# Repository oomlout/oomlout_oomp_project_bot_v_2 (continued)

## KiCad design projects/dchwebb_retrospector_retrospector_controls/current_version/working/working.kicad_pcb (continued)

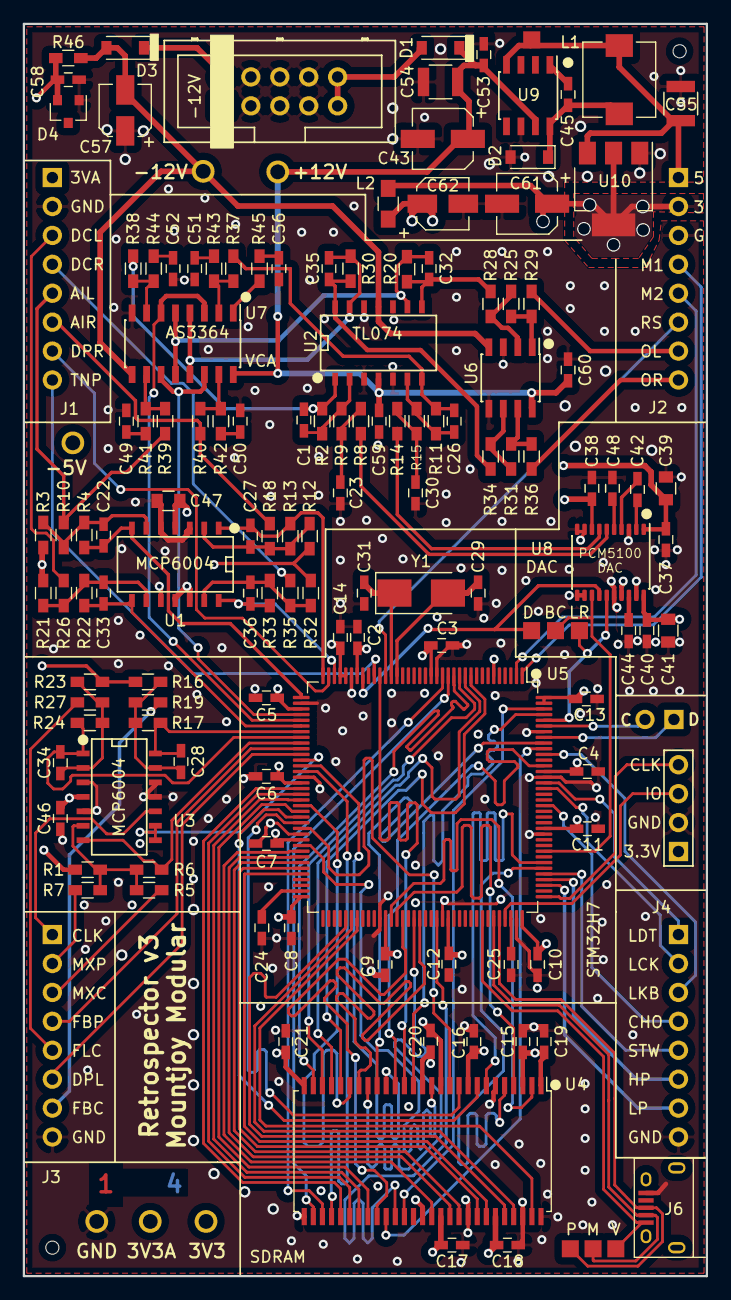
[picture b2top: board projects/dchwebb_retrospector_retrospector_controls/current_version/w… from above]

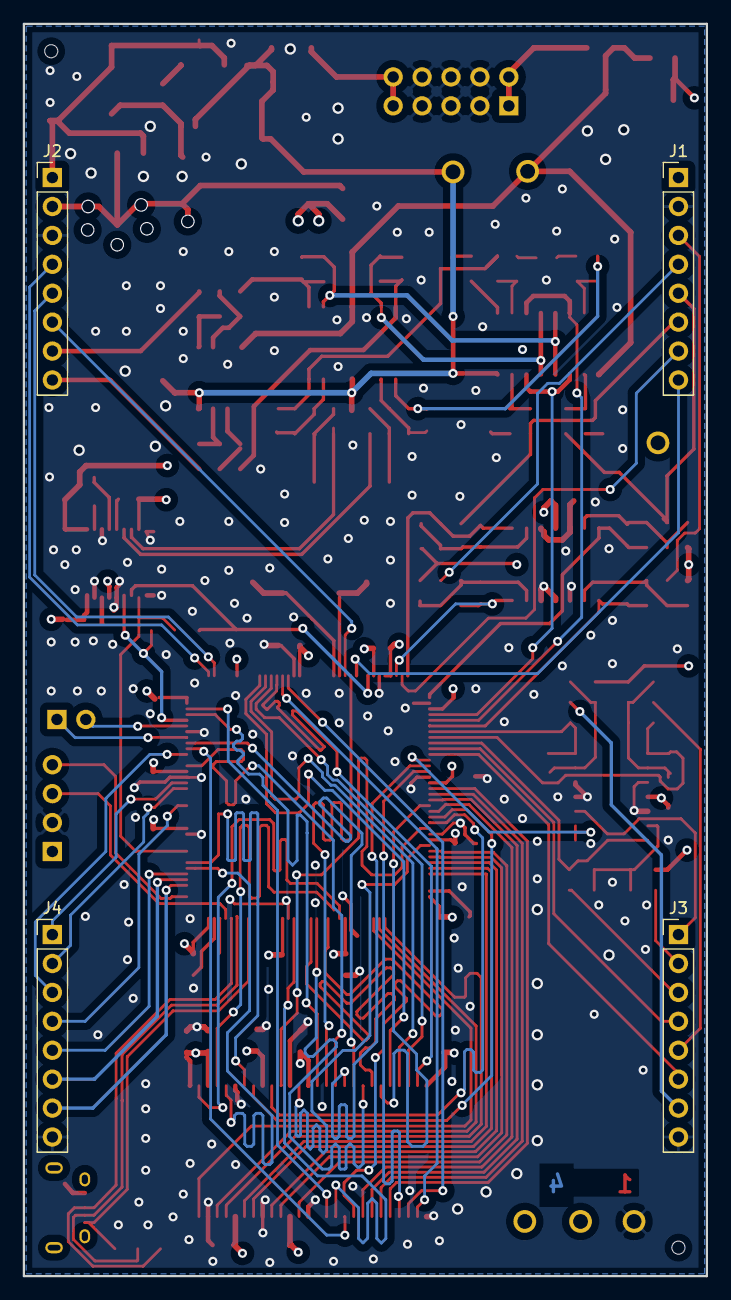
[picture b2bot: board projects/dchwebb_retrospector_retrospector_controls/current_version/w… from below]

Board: 4 copper layers, 60.0 x 110.0 mm, 149 parts (4 on the bottom side), 136 nets.

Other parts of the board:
4_Layer_Marker: 4_Layer_Markers

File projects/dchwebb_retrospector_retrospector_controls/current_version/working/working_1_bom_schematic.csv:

"Source:","C:\gh\oomlout_oomp_project_bot_v_2\projects\dchwebb_retrospector_retrospector_controls\current_version\working\working_1.kicad_sch"
"Date:","01/10/2023 06:39:55"
"Tool:","Eeschema 7.0.6"
"Generator:","C:/Program Files/KiCad/7.0/bin/scripting/plugins/bom_csv_grouped_by_value_with_fp.py"
"Component Count:","149"
"Ref","Qnty","Value","Cmp name","Footprint","Description","Vendor","DNP"
"C1, C26, C32, C35","4","100pF","C_Small","Capacitors_SMD:C_0603_HandSoldering","Unpolarized capacitor, small symbol","",""
"C2, C3, C4, C5, C6, C7, C8, C9, C10, C11, C12, C13, C14, C15, C16, C17, C18, C19, C20, C21, C37, C38, C40, C44, C53, C58","26","100nF","C_Small","Capacitors_SMD:C_0603_HandSoldering","Unpolarized capacitor, small symbol","",""
"C22, C27, C28, C33, C34, C36","6","1.5nF","C_Small","Capacitors_SMD:C_0603_HandSoldering","Unpolarized capacitor, small symbol","",""
"C23, C30","2","1nF","C_Small","Capacitors_SMD:C_0603_HandSoldering","Unpolarized capacitor, small symbol","",""
"C24, C25, C42, C46, C48, C59, C60","7","2.2uF","C_Small","Capacitors_SMD:C_0603_HandSoldering","Unpolarized capacitor, small symbol","",""
"C29, C31","2","30pF","C_Small","Capacitors_SMD:C_0603_HandSoldering","Unpolarized capacitor, small symbol","",""
"C39, C41, C47","3","10uF","C_Small","Capacitors_SMD:C_0805","Unpolarized capacitor, small symbol","",""
"C43, C61","2","47uF","CP_Small","Capacitors_SMD:CP_Elec_5x5.8","","",""
"C45, C56","2","10nF","C_Small","Capacitors_SMD:C_0603_HandSoldering","Unpolarized capacitor, small symbol","",""
"C49, C50, C51, C52","4","560pF","C_Small","Capacitors_SMD:C_0603_HandSoldering","Unpolarized capacitor, small symbol","",""
"C54","1","22uF","C_Small","Capacitors_SMD:C_1210","Unpolarized capacitor, small symbol","",""
"C55","1","47uF","C_Small","Capacitors_SMD:C_1210","Unpolarized capacitor, small symbol","",""
"C57, C62","2","22uF","CP_Small","Capacitors_SMD:CP_Elec_4x5.8","","",""
"D1, D2, D3","3","1N5819","1N5819","Diodes_SMD:D_SOD-123","40V 1A Schottky Barrier Rectifier Diode, DO-41","",""
"D4","1","LM4040DBZ-5","LM4040DBZ-10","TO_SOT_Packages_SMD:SOT-23","10.00V Precision Micropower Shunt Voltage Reference, SOT-23","",""
"H1, H2","2","JLC_Tooling_Hole","MountingHole","Custom_Footprints:JLC_SMT_Tooling_Hole","Mounting Hole without connection","",""
"J1, J2, J3, J4","4","Conn_01x08_Male","Conn_01x08_Male","Pin_Headers:Pin_Header_Straight_1x08_Pitch2.54mm","Generic connector, single row, 01x08, script generated (kicad-library-utils/schlib/autogen/connector/)","",""
"J5","1","SWD_Header","Conn_01x04_Male","Custom_Footprints:SWD_header","Generic connector, single row, 01x04, script generated (kicad-library-utils/schlib/autogen/connector/)","",""
"J6","1","USB_B_Micro","USB_B_Micro","Custom_Footprints:USB_Micro-B_Amphenol","USB Micro Type B connector","",""
"J7","1","Eurorack_10_pin_power","Eurorack_10_pin_power","Custom_Footprints:Eurorack_10_pin_header","","",""
"J8","1","I2C_TestPoint","Conn_01x02_Female","Pin_Headers:Pin_Header_Straight_1x02_Pitch2.54mm","Generic connector, single row, 01x02, script generated (kicad-library-utils/schlib/autogen/connector/)","",""
"L1","1","68uH","L_Small","Custom_Footprints:TDK_Inductor_6.9x7.2","Inductor, small symbol","",""
"L2","1","L","L","Inductors_SMD:L_0805_HandSoldering","Inductor","",""
"R1","1","75k","R","Resistors_SMD:R_0603_HandSoldering","Resistor","",""
"R2, R6, R7, R10, R11, R18, R22, R24, R33","9","47k","R","Resistors_SMD:R_0603_HandSoldering","Resistor","",""
"R3, R12","2","20k","R","Resistors_SMD:R_0603_HandSoldering","Resistor","",""
"R4, R13","2","6k8","R","Resistors_SMD:R_0603_HandSoldering","Resistor","",""
"R5, R16","2","91k","R","Resistors_SMD:R_0603_HandSoldering","Resistor","",""
"R8, R14, R46","3","2k2","R_Small","Resistors_SMD:R_0603_HandSoldering","Resistor, small symbol","",""
"R9, R15, R25, R28, R31, R34","6","10k","R","Resistors_SMD:R_0603_HandSoldering","Resistor","",""
"R17","1","56k","R","Resistors_SMD:R_0603_HandSoldering","Resistor","",""
"R19, R26, R27, R35","4","100k","R","Resistors_SMD:R_0603_HandSoldering","Resistor","",""
"R20, R30, R37, R38, R39, R40","6","30k","R_Small","Resistors_SMD:R_0603_HandSoldering","Resistor, small symbol","",""
"R21, R23, R32","3","68k","R","Resistors_SMD:R_0603_HandSoldering","Resistor","",""
"R29, R36","2","1k","R","Resistors_SMD:R_0603_HandSoldering","Resistor","",""
"R41, R42, R43, R44","4","510R","R_Small","Resistors_SMD:R_0603_HandSoldering","Resistor, small symbol","",""
"R45","1","100R","R_Small","Resistors_SMD:R_0603_HandSoldering","Resistor, small symbol","",""
"TP1, TP2, TP3, TP4, TP5, TP6","6","TestPoint","TestPoint","Custom_Footprints:1.3mm_Test_Point","test point","",""
"TP7, TP8, TP9, TP10, TP11, TP12, TP13","7","TestPoint","TestPoint","Measurement_Points:Measurement_Point_Square-SMD-Pad_Small","test point","",""
"U1, U3","2","MCP6004","MCP6004","SMD_Packages:SOIC-14_N","1MHz, Low-Power Op Amp, DIP-14/SOIC-14/TSSOP-14","",""
"U2","1","TL074","TL074","SMD_Packages:SOIC-14_N","Quad Low-Noise JFET-Input Operational Amplifiers, DIP-14/SOIC-14","",""
"U4","1","IS42S16800F-7TLI","IS42S16160","Custom_Footprints:TSOP-II-54_22.2x10.16mm_P0.8mm","","",""
"U5","1","STM32H743ZITx","STM32H743ZITx","Package_QFP:LQFP-144_20x20mm_P0.5mm","ARM Cortex-M7 MCU, 2048KB flash, 864KB RAM, 400MHz, 1.7-3.6V, 114 GPIO, LQFP-144","",""
"U6","1","TL072","TL072","Housings_SOIC:SOIC-8_3.9x4.9mm_Pitch1.27mm","Dual Low-Noise JFET-Input Operational Amplifiers, DIP-8/SOIC-8","",""
"U7","1","AS3364","SSI2164","Housings_SOIC:SOIC-16_3.9x9.9mm_Pitch1.27mm","Quad VCA, SOIC-16","",""
"U8","1","PCM5100APW","PCM5100APW","Custom_Footprints:SSOP-20_4.4x6.5mm_Pitch0.65mm_Round_Pads","2VRMS DirectPath, 100dB Audio Stereo DAC with 32-bit, 384kHz PCM Interface, TSSOP-20","",""
"U9","1","LM2675M-5","LM2675M-5","Housings_SOIC:SOIC-8_3.9x4.9mm_Pitch1.27mm","5V, 1A Step-Down Voltage Regulator, SO-8","",""
"U10","1","LD1117-3.3-4Tab","LD1117-3.3-4Tab","TO_SOT_Packages_SMD:SOT-223-3_TabPin2","1A Low Dropout regulator, positive, 3.3V fixed output, SOT-223","",""
"U11","1","Hyperram_BGA","Hyperram_BGA","","","",""
"Y1","1","8MHz 20pF","Crystal","Crystals:Crystal_SMD_5032-2pin_5.0x3.2mm_HandSoldering","Two pin crystal","",""

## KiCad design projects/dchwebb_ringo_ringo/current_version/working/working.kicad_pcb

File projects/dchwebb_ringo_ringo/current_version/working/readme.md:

# ringo
 
## summary 
* id: dchwebb_ringo_ringo
* user: dchwebb
* name: ringo
* board: ringo
* repo: https://github.com/dchwebb/Ringo
* src_file_repo_kicad_pcb: Ringo.kicad_pcb
* src_file_repo_kicad_pcb_link: https://github.com/dchwebb/Ringo/tree/master/Ringo.kicad_pcb
* src_file_repo_kicad_sch: Ringo.kicad_sch
* src_file_repo_kicad_sch_link: https://github.com/dchwebb/Ringo/tree/master/Ringo.kicad_sch

* src_file_repo_sch: 
* src_file_repo_sch_link: https://github.com/dchwebb/Ringo/tree/master/
* full details link: https://github.com/oomlout/oomlout_oomp_project_bot_v_2/tree/main/projects/dchwebb_ringo_ringo/current_version/working

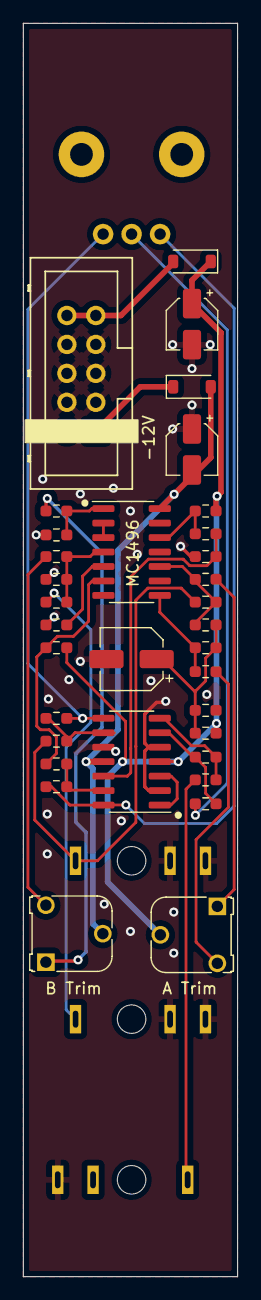
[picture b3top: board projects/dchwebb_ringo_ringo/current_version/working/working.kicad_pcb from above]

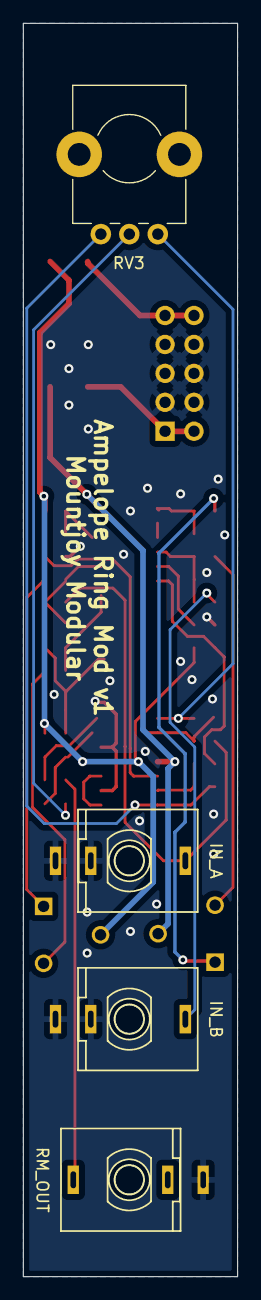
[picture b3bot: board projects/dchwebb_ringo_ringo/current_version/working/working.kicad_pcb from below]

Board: 2 copper layers, 18.8 x 110.0 mm, 38 parts (4 on the bottom side), 30 nets.

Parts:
C1: 100uF 16V; CP_Elec_5x5.7
C2, C3: 22uF; CP_Elec_4x5.8
D1, D2: 1N5819; D_SOD-123
J1: IN_A; THONKICONN_hole
J2: IN_B; THONKICONN_hole
J3: RM_OUT; THONKICONN_hole
J4: Eurorack_10_pin_power; Eurorack_10_pin_header
R1, R2: 1K5; R_0603_1608Metric_Pad0.98x0.95mm_HandSolder
R3, R4: 12K; R_0603_1608Metric_Pad0.98x0.95mm_HandSolder
R5, R7, R19, R22: 2K7; R_0603_1608Metric_Pad0.98x0.95mm_HandSolder
R6, R12, R15, R18, R23, R24: 15K; R_0603_1608Metric_Pad0.98x0.95mm_HandSolder
R8, R9: 1K2; R_0603_1608Metric_Pad0.98x0.95mm_HandSolder
R10: 68K; R_0603_1608Metric_Pad0.98x0.95mm_HandSolder
R11, R16: 180K; R_0603_1608Metric_Pad0.98x0.95mm_HandSolder
R13: 10K; R_0603_1608Metric_Pad0.98x0.95mm_HandSolder
R14: 470; R_0603_1608Metric_Pad0.98x0.95mm_HandSolder
R17, R20, R21: 6K8; R_0603_1608Metric_Pad0.98x0.95mm_HandSolder
RV1: 500; Potentiometer_Runtron_RM-065_Vertical
RV2: 220; Potentiometer_Runtron_RM-065_Vertical
RV3: R_Potentiometer; Alpha_9mm_Potentiometer_Aligned
U1: MC1496; SOIC-14_3.9x8.7mm_P1.27mm
U2: TL074; SOIC-14_3.9x8.7mm_P1.27mm

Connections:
+12V: D1.2 (A), J4.9, J4.10
-12V: D2.1 (K), J4.1, J4.2
/A_IN: J1.3, R11.2, R23.2
/MIX_OUT: R13.2, RV3.2
/MIX_RM: R6.1, RV3.3, U2.14
GND: C1.2, C2.2, C3.1, J1.1, J1.2, J2.1, J2.2, J3.1, J4.3, J4.4, J4.5, J4.6, J4.7, J4.8, R1.2, R17.1, R18.1, R19.1, R22.1, U2.2 (-), U2.5 (+), U2.10 (+)
unnamed: C1.1, R1.1, R2.2, R5.2, R7.2
unnamed: J2.3, R16.2
unnamed: J3.3, R14.1
unnamed: R3.1, RV1.1
unnamed: R4.1, RV1.3
unnamed: R4.2, R5.1, U1.8 (C_IN)
unnamed: R10.1, R14.2, U2.7
unnamed: R10.2, R13.1, U2.6 (-)
unnamed: R3.2, R7.1, R11.1, U1.10 (C_IN)
unnamed: R6.2, R12.1, U2.13 (-)
unnamed: R8.2, R12.2, U1.6 (OUT)
unnamed: R15.1, R18.2, U2.12 (+)
unnamed: R9.2, R15.2, U1.12 (OUT)
unnamed: R16.1, R19.2, R20.2, U1.4 (S_IN)
unnamed: R17.2, U1.5 (BIAS)
unnamed: R20.1, RV2.3
unnamed: R21.1, RV2.1
unnamed: R21.2, R22.2, U1.1 (S_IN)
unnamed: R23.1, R24.2, U2.9 (-)
unnamed: R24.1, RV3.1, U2.8
unnamed: U1.2 (GAIN), U1.3 (GAIN)
unnamed: U2.1, U2.3 (+)
VCC: C2.1, D1.1 (K), R2.1, R8.1, R9.1, RV1.2, U2.4 (V+)
VEE: C3.2, D2.2 (A), RV2.2, U1.14 (VEE), U2.11 (V-)

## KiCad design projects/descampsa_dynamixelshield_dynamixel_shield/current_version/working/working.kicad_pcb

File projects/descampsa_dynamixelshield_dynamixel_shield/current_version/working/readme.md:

# dynamixelshield
 
## summary 
* id: descampsa_dynamixelshield_dynamixel_shield
* user: descampsa
* name: dynamixelshield
* board: dynamixel_shield
* repo: https://github.com/descampsa/DynamixelShield
* src_file_repo_kicad_pcb: dynamixel_shield.kicad_pcb
* src_file_repo_kicad_pcb_link: https://github.com/descampsa/DynamixelShield/tree/master/dynamixel_shield.kicad_pcb

* src_file_repo_sch: dynamixel_shield.sch
* src_file_repo_sch_link: https://github.com/descampsa/DynamixelShield/tree/master/dynamixel_shield.sch
* full details link: https://github.com/oomlout/oomlout_oomp_project_bot_v_2/tree/main/projects/descampsa_dynamixelshield_dynamixel_shield/current_version/working

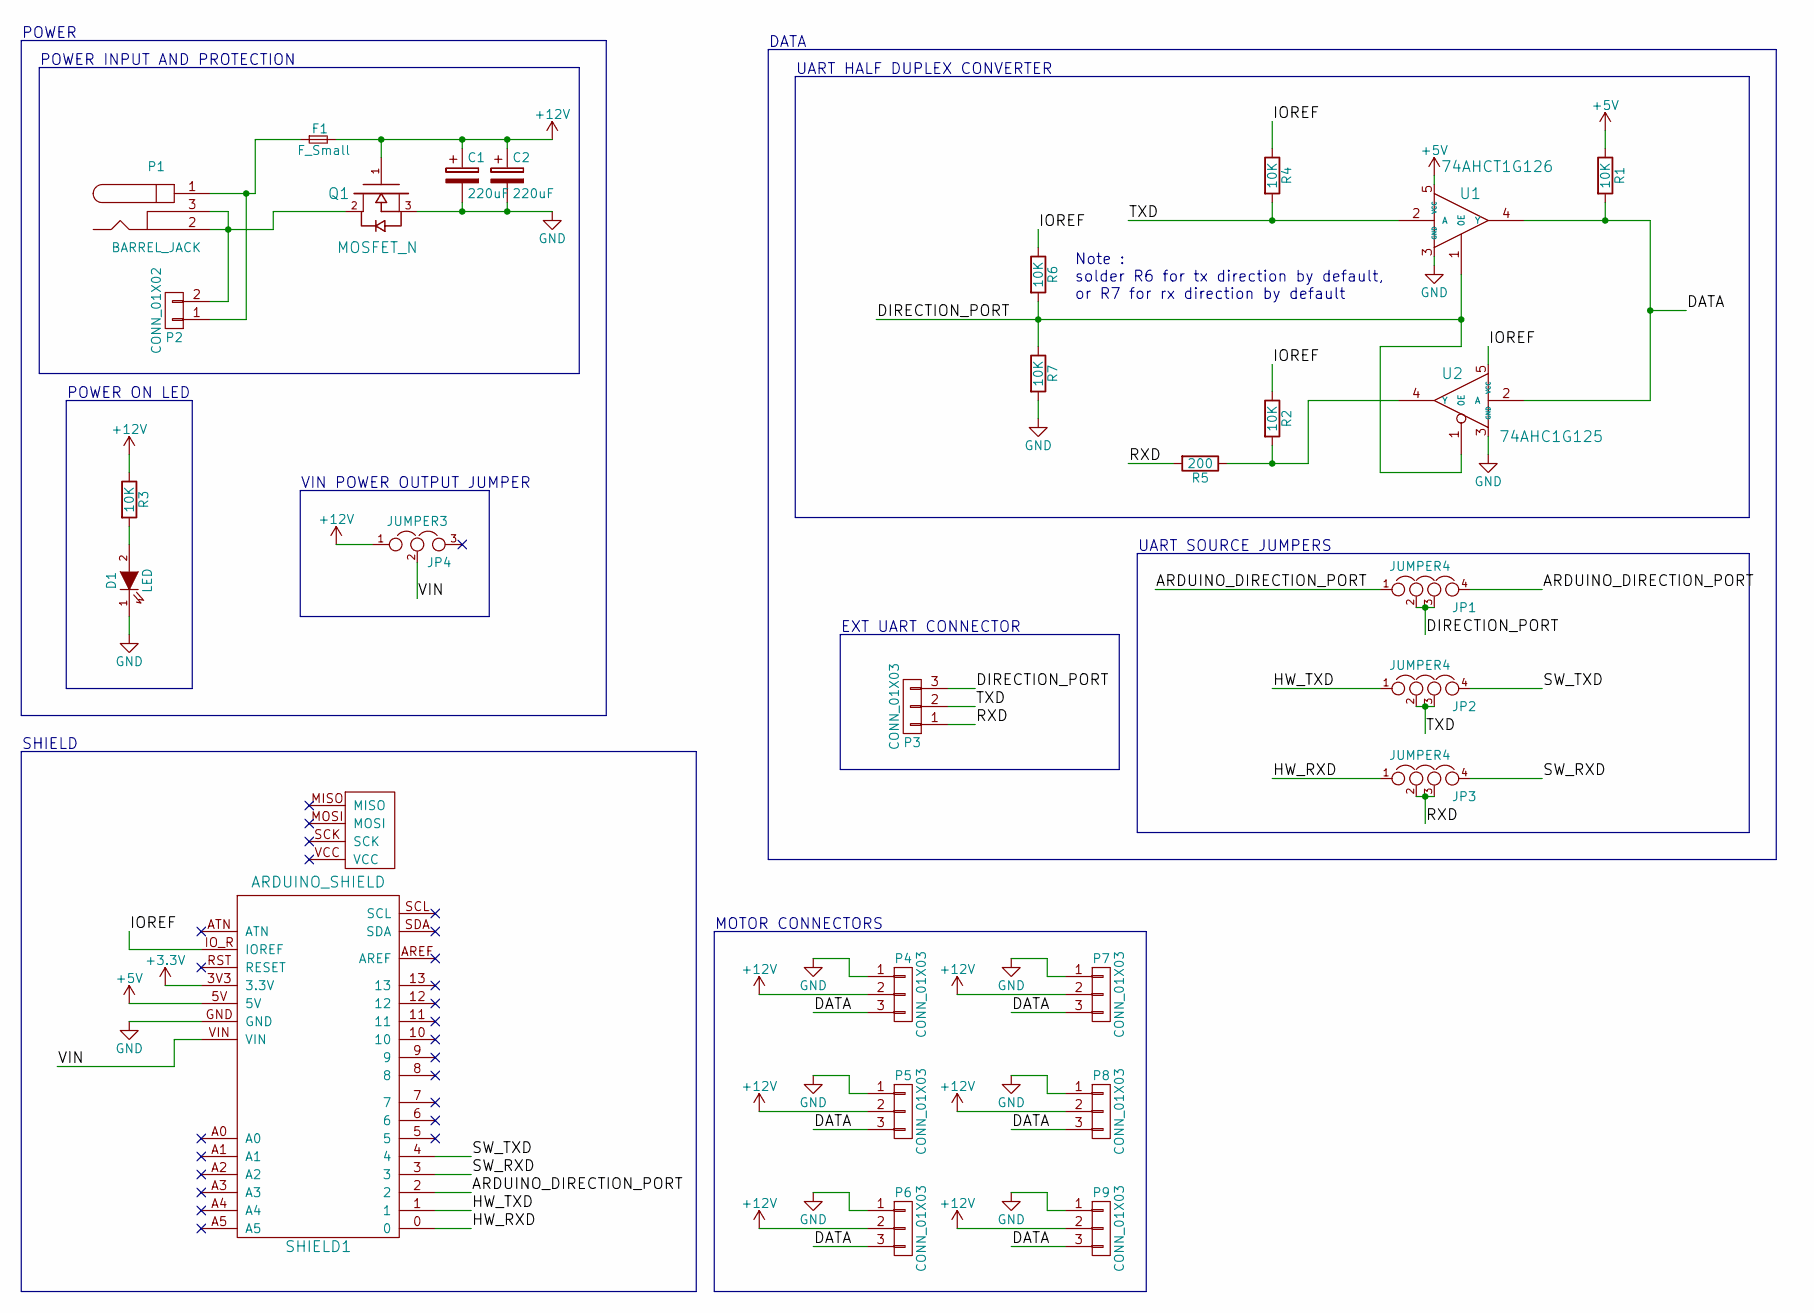
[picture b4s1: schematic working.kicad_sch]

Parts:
C1, C2: 220uF; CP_Elec_6.3x7.7
D1: LED; LED_0603
F1: F_Small; Fuseholder5x20_horiz_lateral
JP1, JP2, JP3: JUMPER4; Pin_Header_Straight_1x04
JP4: JUMPER3; Pin_Header_Straight_1x03
P1: BARREL_JACK
P2: CONN_01X02; bornier2
P3: CONN_01X03; Pin_Header_Angled_1x03
P4, P5, P6, P7: CONN_01X03; Molex_spox_1x3_right
P8, P9: CONN_01X03; Molex_spox_1x3_straight
Q1: MOSFET_N; TO-252-2Lead
R1, R2, R3, R4, R6, R7: 10K; R_0603_HandSoldering
R5: 200; R_0603_HandSoldering
SHIELD1: ARDUINO_SHIELD; Arduino_shield_dynamixel
U1: 74AHCT1G126; SOT-353
U2: 74AHC1G125; SOT-353

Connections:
+3V3: SHIELD1.3V3 (3.3V)
+5V: R1.1, SHIELD1.5V, U1.5 (VCC)
+12V: C1.1, C2.1, F1.2, JP4.1, P4.2, P5.2, P6.2, P7.2, P8.2, P9.2, Q1.1 (G), R3.1
/ARDUINO_DIRECTION_PORT: JP1.1, JP1.4, SHIELD1.2
/DATA: P4.3, P5.3, P6.3, P7.3, P8.3, P9.3, R1.2, U1.4 (Y), U2.2 (A)
/DIRECTION_PORT: JP1.2, JP1.3, P3.3, R6.2, R7.1, U1.1 (0E), U2.1 (0E)
/HW_RXD: JP3.1, SHIELD1.0
/HW_TXD: JP2.1, SHIELD1.1
/IOREF: R2.1, R4.1, R6.1, SHIELD1.IO_R (IOREF), U2.5 (VCC)
/RXD: JP3.2, JP3.3, P3.1, R5.2
/SW_RXD: JP3.4, SHIELD1.3
/SW_TXD: JP2.4, SHIELD1.4
/TXD: JP2.2, JP2.3, P3.2, R4.2, U1.2 (A)
/VIN: JP4.2, SHIELD1.VIN
GND: C1.2, C2.2, D1.1 (K), P4.1, P5.1, P6.1, P7.1, P8.1, P9.1, Q1.3 (S), R7.2, SHIELD1.GND, U1.3 (GND), U2.3 (GND)
unnamed: D1.2 (A), R3.2
unnamed: F1.1, P1.1, P2.1
unnamed: P1.2, P1.3, P2.2, Q1.2 (D)
unnamed: R2.2, R5.1, U2.4 (Y)

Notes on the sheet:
EXT UART CONNECTOR
SHIELD
POWER
DATA
VIN POWER OUTPUT JUMPER
Note : solder R6 for tx direction by default, or R7 for rx direction by default
UART HALF DUPLEX CONVERTER
POWER INPUT AND PROTECTION
MOTOR CONNECTORS
POWER ON LED
UART SOURCE JUMPERS

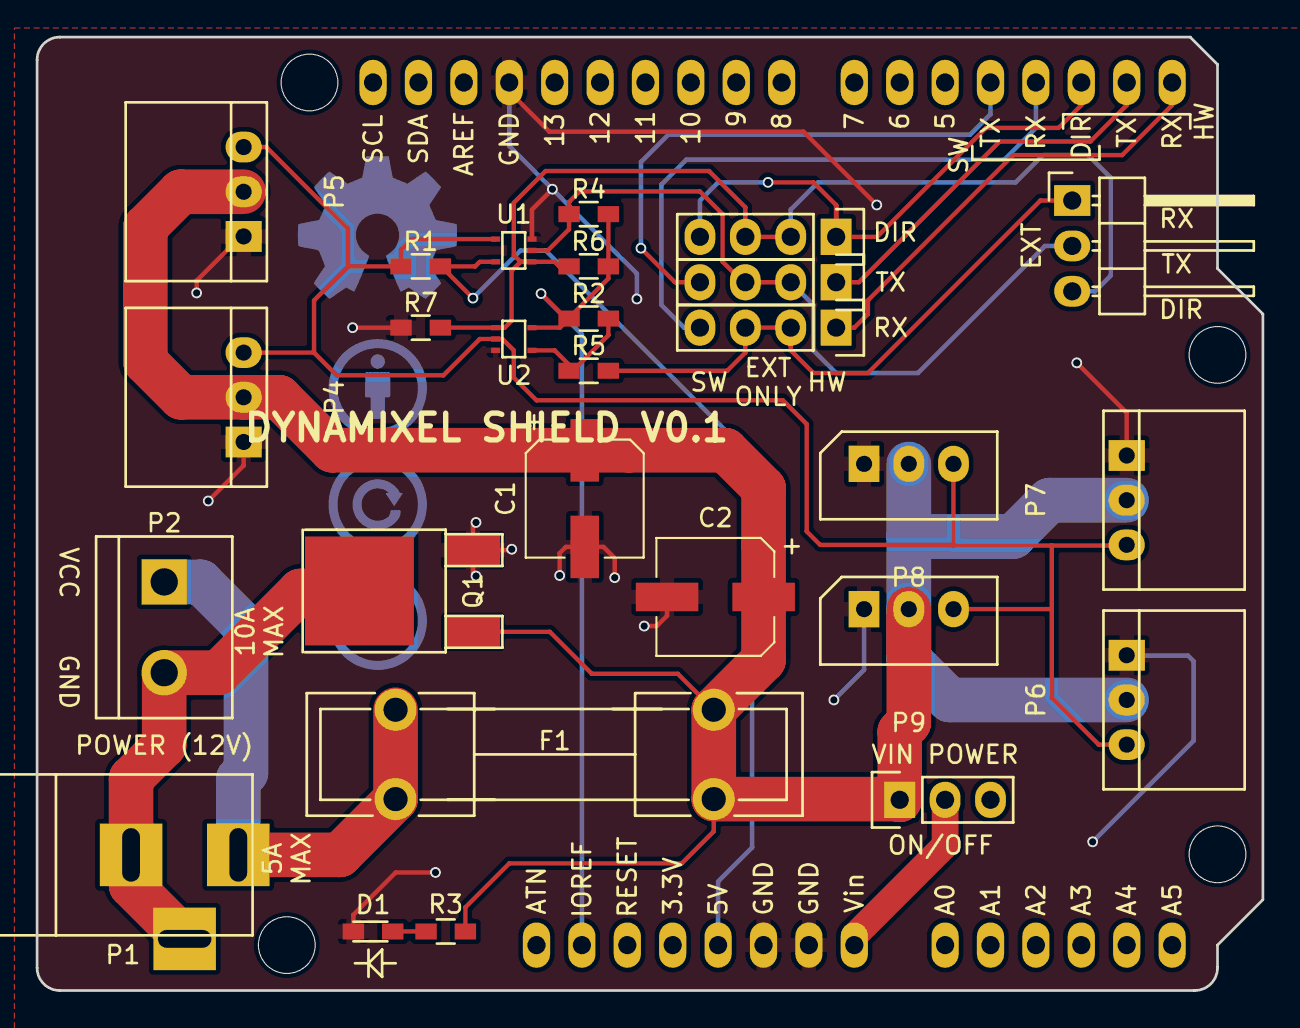
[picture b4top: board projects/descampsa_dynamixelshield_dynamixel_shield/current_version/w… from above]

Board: 2 copper layers, 68.6 x 53.3 mm, 28 parts (0 on the bottom side), 18 nets.

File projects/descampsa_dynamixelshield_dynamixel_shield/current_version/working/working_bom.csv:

"Id";"Designator";"Footprint";"Quantity";"Designation";"Supplier and ref";
1;"JP1,JP2,JP3";"Pin_Header_Straight_1x04";3;"JUMPER4";;;
2;"JP4";"Pin_Header_Straight_1x03";1;"JUMPER3";;;
3;"P2";"bornier2";1;"CONN_01X02";;;
4;"P3";"Pin_Header_Angled_1x03";1;"CONN_01X03";;;
5;"P4,P5,P6,P7";"Molex_spox_1x3_right";4;"CONN_01X03";;;
6;"P8,P9";"Molex_spox_1x3_straight";2;"CONN_01X03";;;
7;"Q1";"TO-252-2Lead";1;"MOSFET_N";;;
8;"R1,R2,R3,R4,R6,R7";"R_0603_HandSoldering";6;"10K";;;
9;"U1";"SOT-353";1;"74AHCT1G126";;;
10;"U2";"SOT-353";1;"74AHC1G125";;;
11;"P1";"BARREL_JACK";1;"BARREL_JACK";;;
12;"F1";"Fuseholder5x20_horiz_lateral";1;"F_Small";;;
13;"D1";"LED_0603";1;"LED";;;
14;"SHIELD1";"Arduino_shield_dynamixel";1;"ARDUINO_SHIELD";;;
15;"R5";"R_0603_HandSoldering";1;"200";;;
16;"C1,C2";"CP_Elec_6.3x7.7";2;"220uF";;;
17;"REF**";"CreativeCommonCopperSmall";1;"CreativeCommonCopper";;;
18;"REF**";"CreativeCommonAttributionCopperSmall";1;"CreativeCommonAttributionCopperSmall";;;
19;"REF**";"CreativeCommonShareAlikeCopperSmall";1;"CreativeCommonShareAlikeCopperSmall";;;

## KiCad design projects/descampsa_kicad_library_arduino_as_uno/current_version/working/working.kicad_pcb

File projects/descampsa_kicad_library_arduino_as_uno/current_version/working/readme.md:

# kicad_library
 
## summary 
* id: descampsa_kicad_library_arduino_as_uno
* user: descampsa
* name: kicad_library
* board: arduino_as_uno
* repo: https://github.com/descampsa/kicad-library
* src_file_repo_kicad_pcb: template/Arduino_As_Uno_R3/Arduino_As_Uno.kicad_pcb
* src_file_repo_kicad_pcb_link: https://github.com/descampsa/kicad-library/tree/master/template/Arduino_As_Uno_R3/Arduino_As_Uno.kicad_pcb

* src_file_repo_sch: template/Arduino_As_Uno_R3/Arduino_As_Uno.sch
* src_file_repo_sch_link: https://github.com/descampsa/kicad-library/tree/master/template/Arduino_As_Uno_R3/Arduino_As_Uno.sch
* full details link: https://github.com/oomlout/oomlout_oomp_project_bot_v_2/tree/main/projects/descampsa_kicad_library_arduino_as_uno/current_version/working

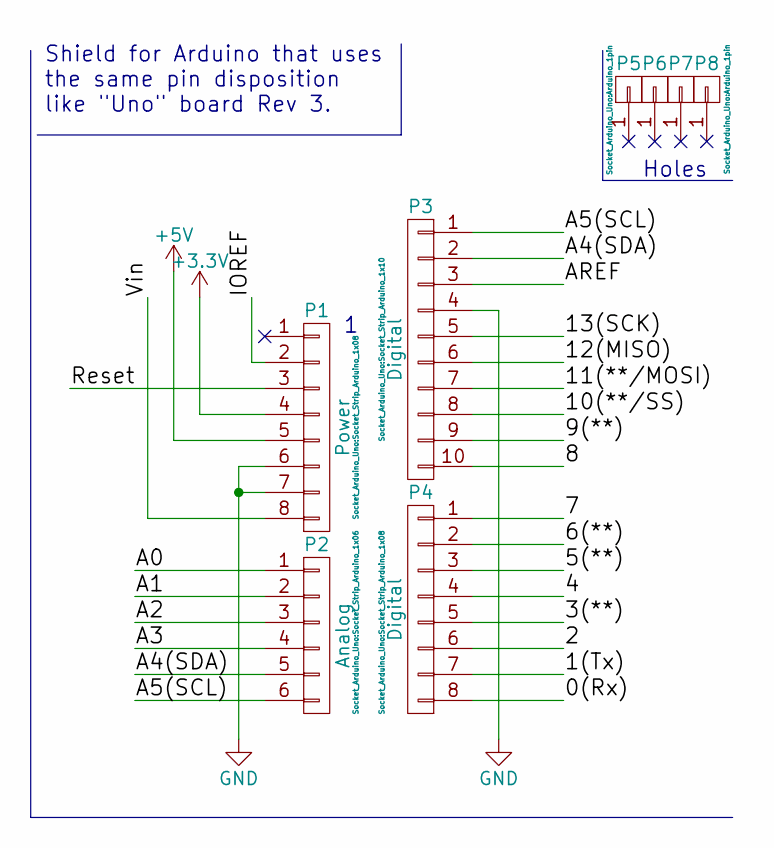
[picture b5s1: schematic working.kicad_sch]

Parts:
P1: Power; Socket_Strip_Arduino_1x08
P2: Analog; Socket_Strip_Arduino_1x06
P3: Digital; Socket_Strip_Arduino_1x10
P4: Digital; Socket_Strip_Arduino_1x08
P5, P6, P7, P8: CONN_01X01; Arduino_1pin

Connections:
+3V3: P1.4
+5V: P1.5
/0(Rx): P4.8
/1(Tx): P4.7
/2: P4.6
/3(**): P4.5
/4: P4.4
/5(**): P4.3
/6(**): P4.2
/7: P4.1
/8: P3.10
/9(**): P3.9
/10(**/SS): P3.8
/11(**/MOSI): P3.7
/12(MISO): P3.6
/13(SCK): P3.5
/A0: P2.1
/A1: P2.2
/A2: P2.3
/A3: P2.4
/A4(SDA): P2.5, P3.2
/A5(SCL): P2.6, P3.1
/AREF: P3.3
/IOREF: P1.2
/Reset: P1.3
/Vin: P1.8
GND: P1.6, P1.7, P3.4

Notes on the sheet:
Holes
Shield for Arduino that uses the same pin disposition like "Uno" board Rev 3.

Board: 2 copper layers, 8 parts (0 on the bottom side), 3 nets, no tracks yet.

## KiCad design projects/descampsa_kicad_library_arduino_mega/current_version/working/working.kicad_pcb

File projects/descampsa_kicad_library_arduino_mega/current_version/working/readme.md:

# kicad_library
 
## summary 
* id: descampsa_kicad_library_arduino_mega
* user: descampsa
* name: kicad_library
* board: arduino_mega
* repo: https://github.com/descampsa/kicad-library
* src_file_repo_kicad_pcb: template/Arduino_Mega_R3/Arduino_Mega.kicad_pcb
* src_file_repo_kicad_pcb_link: https://github.com/descampsa/kicad-library/tree/master/template/Arduino_Mega_R3/Arduino_Mega.kicad_pcb

* src_file_repo_sch: template/Arduino_Mega_R3/Arduino_Mega.sch
* src_file_repo_sch_link: https://github.com/descampsa/kicad-library/tree/master/template/Arduino_Mega_R3/Arduino_Mega.sch
* full details link: https://github.com/oomlout/oomlout_oomp_project_bot_v_2/tree/main/projects/descampsa_kicad_library_arduino_mega/current_version/working

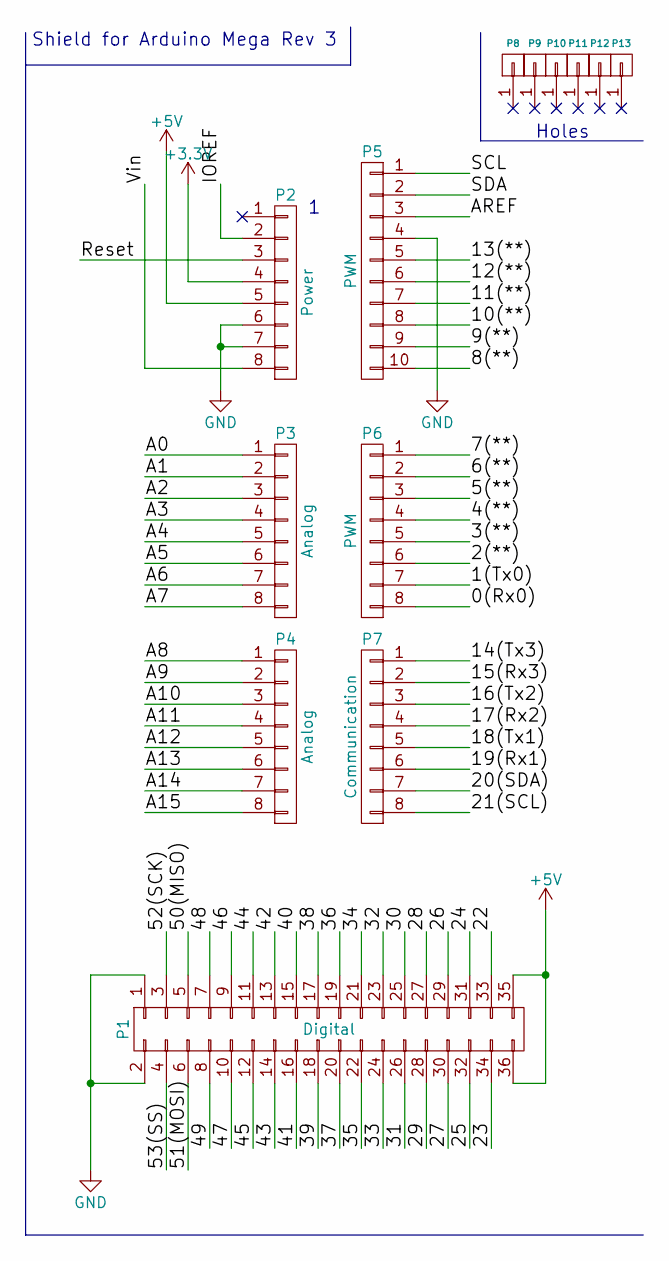
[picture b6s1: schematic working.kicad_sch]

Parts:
P1: Digital; Socket_Strip_Arduino_2x18
P2: Power; Socket_Strip_Arduino_1x08
P3, P4: Analog; Socket_Strip_Arduino_1x08
P5: PWM; Socket_Strip_Arduino_1x10
P6: PWM; Socket_Strip_Arduino_1x08
P7: Communication; Socket_Strip_Arduino_1x08
P8, P9, P10, P11, P12, P13: CONN_01X01; Arduino_1pin

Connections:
+3V3: P2.4
+5V: P1.35, P1.36, P2.5
/0(Rx0): P6.8
/1(Tx0): P6.7
/2(**): P6.6
/3(**): P6.5
/4(**): P6.4
/5(**): P6.3
/6(**): P6.2
/7(**): P6.1
/8(**): P5.10
/9(**): P5.9
/10(**): P5.8
/11(**): P5.7
/12(**): P5.6
/13(**): P5.5
/14(Tx3): P7.1
/15(Rx3): P7.2
/16(Tx2): P7.3
/17(Rx2): P7.4
/18(Tx1): P7.5
/19(Rx1): P7.6
/20(SDA): P7.7
/21(SCL): P7.8
/22: P1.33
/23: P1.34
/24: P1.31
/25: P1.32
/26: P1.29
/27: P1.30
/28: P1.27
/29: P1.28
/30: P1.25
/31: P1.26
/32: P1.23
/33: P1.24
/34: P1.21
/35: P1.22
/36: P1.19
/37: P1.20
/38: P1.17
/39: P1.18
/40: P1.15
/41: P1.16
/42: P1.13
/43: P1.14
/44: P1.11
/45: P1.12
/46: P1.9
/47: P1.10
/48: P1.7
/49: P1.8
/50(MISO): P1.5
/51(MOSI): P1.6
/52(SCK): P1.3
/53(SS): P1.4
/A0: P3.1
/A1: P3.2
/A2: P3.3
/A3: P3.4
/A4: P3.5
/A5: P3.6
/A6: P3.7
/A7: P3.8
/A8: P4.1
/A9: P4.2
/A10: P4.3
/A11: P4.4
/A12: P4.5
/A13: P4.6
/A14: P4.7
/A15: P4.8
/AREF: P5.3
/IOREF: P2.2
/Reset: P2.3
/SCL: P5.1
/SDA: P5.2
/Vin: P2.8
GND: P1.1, P1.2, P2.6, P2.7, P5.4

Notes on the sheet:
Holes
Shield for Arduino Mega Rev 3

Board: 2 copper layers, 13 parts (0 on the bottom side), 2 nets, no tracks yet.

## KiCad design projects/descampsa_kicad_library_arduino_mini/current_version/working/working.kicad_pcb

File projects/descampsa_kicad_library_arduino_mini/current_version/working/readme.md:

# kicad_library
 
## summary 
* id: descampsa_kicad_library_arduino_mini
* user: descampsa
* name: kicad_library
* board: arduino_mini
* repo: https://github.com/descampsa/kicad-library
* src_file_repo_kicad_pcb: template/Arduino_Mini/Arduino_Mini.kicad_pcb
* src_file_repo_kicad_pcb_link: https://github.com/descampsa/kicad-library/tree/master/template/Arduino_Mini/Arduino_Mini.kicad_pcb

* src_file_repo_sch: template/Arduino_Mini/Arduino_Mini.sch
* src_file_repo_sch_link: https://github.com/descampsa/kicad-library/tree/master/template/Arduino_Mini/Arduino_Mini.sch
* full details link: https://github.com/oomlout/oomlout_oomp_project_bot_v_2/tree/main/projects/descampsa_kicad_library_arduino_mini/current_version/working

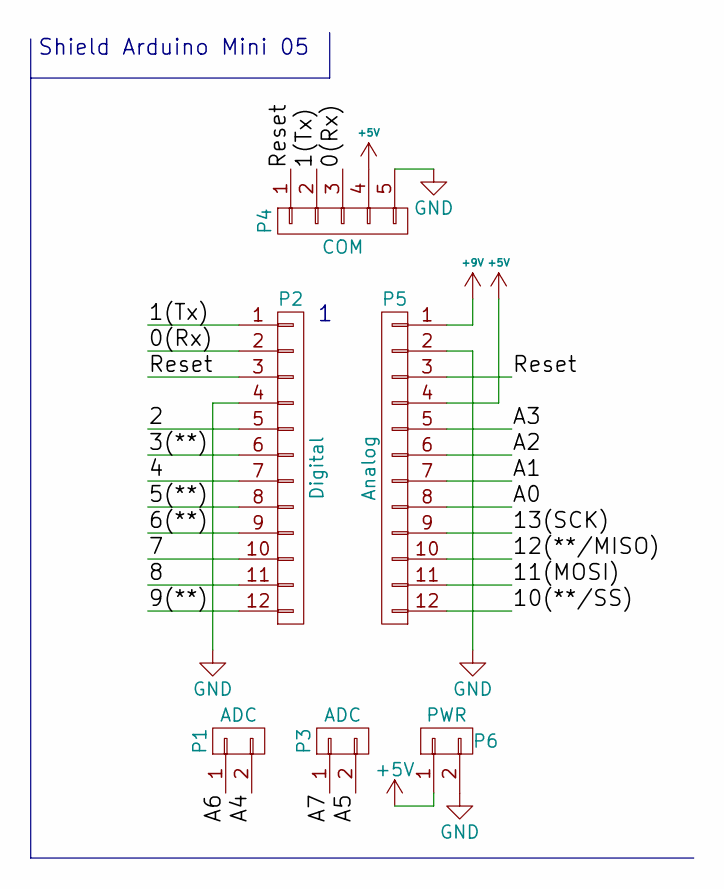
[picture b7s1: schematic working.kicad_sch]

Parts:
P1, P3: ADC; Socket_Strip_Arduino_1x02
P2: Digital; Socket_Strip_Arduino_1x12
P4: COM; Socket_Strip_Arduino_1x05
P5: Analog; Socket_Strip_Arduino_1x12
P6: PWR; Socket_Strip_Arduino_1x02

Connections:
+5V: P4.4, P5.4, P6.1
+9V: P5.1
/0(Rx): P2.2, P4.3
/1(Tx): P2.1, P4.2
/2: P2.5
/3(**): P2.6
/4: P2.7
/5(**): P2.8
/6(**): P2.9
/7: P2.10
/8: P2.11
/9(**): P2.12
/10(**/SS): P5.12
/11(MOSI): P5.11
/12(**/MISO): P5.10
/13(SCK): P5.9
/A0: P5.8
/A1: P5.7
/A2: P5.6
/A3: P5.5
/A4: P1.2
/A5: P3.2
/A6: P1.1
/A7: P3.1
/Reset: P2.3, P4.1, P5.3
GND: P2.4, P4.5, P5.2, P6.2

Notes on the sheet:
Shield Arduino Mini 05

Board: 2 copper layers, 6 parts (0 on the bottom side), 5 nets, no tracks yet.
